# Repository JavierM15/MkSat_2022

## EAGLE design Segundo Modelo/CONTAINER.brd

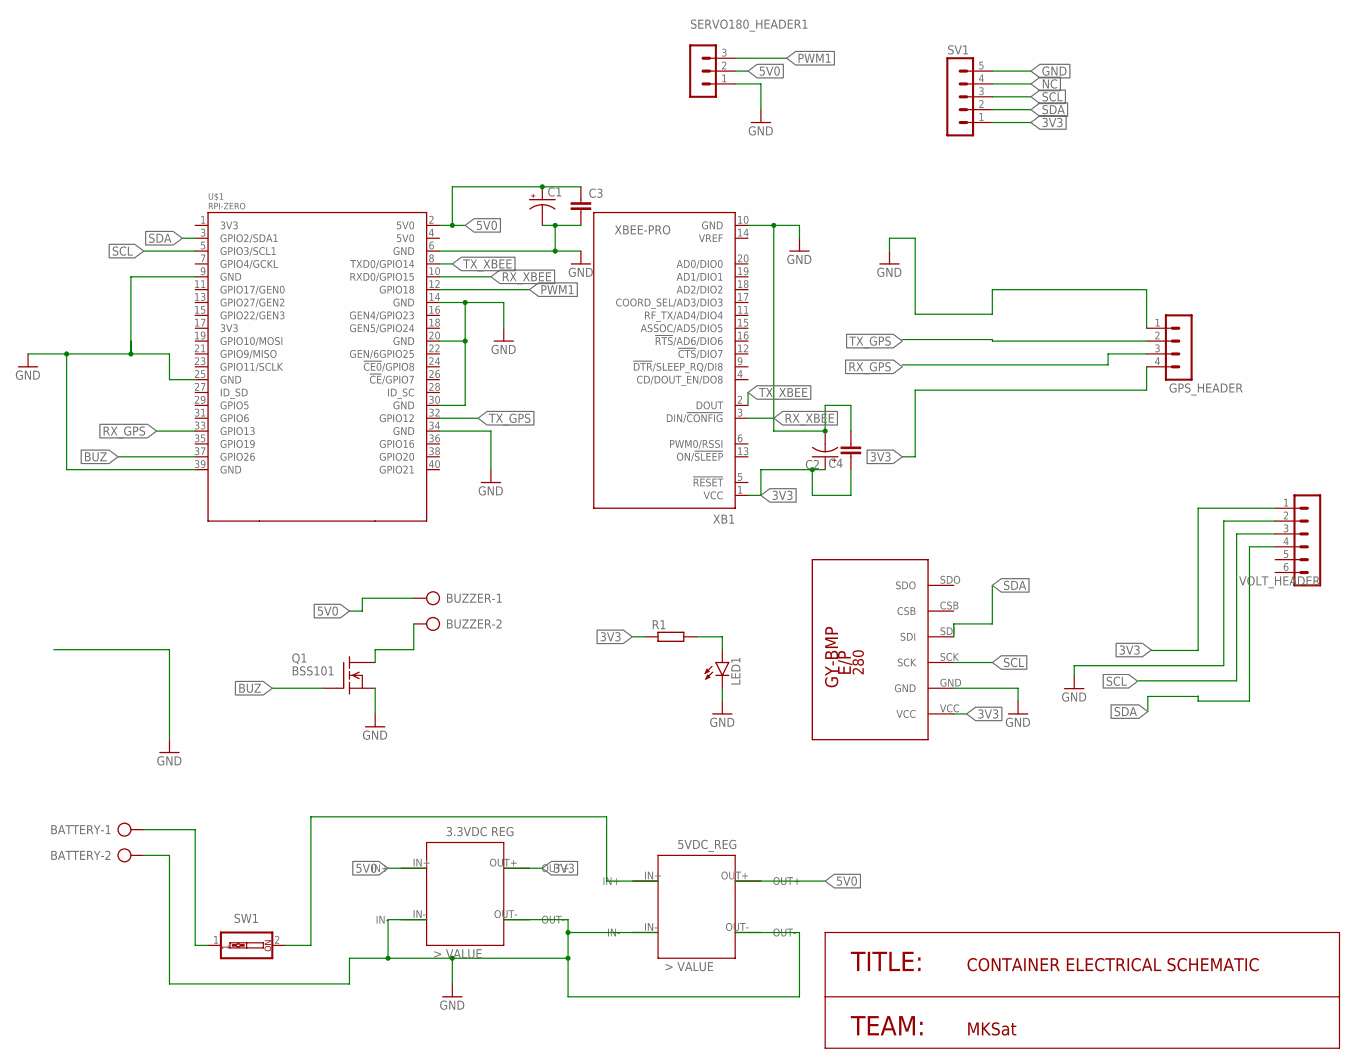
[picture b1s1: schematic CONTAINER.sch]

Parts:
BATTERY: AK500/2
BUZZER: AK500/2
C1, C2: CPOL-USTAP5-45; TAP5-45
C3, C4: C-EU050-030X075; C050-030X075
GPS_HEADER: MA04-1
LED1: LED5MM
Q1: BSS101; TO92
R1: R-EU_0207/12; 0207/12
SERVO180_HEADER1: MA03-1
SV1: MA05-1
SW1: SW_DIP-1; EDG-01
U$1: RPI-ZERO; RASPBERRYPI_BASTELSTUBE_V13_RASPI_BOARD_B+_FULL
U$4: GY-BPM280; GY-BMP280-FOOTPRINT
U$5: 3VDC_REG
U$6: 5VDC_REG
VOLT_HEADER: MA06-1
XB1: XBEE-PRO

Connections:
3V3: C2.+, C4.1, GPS_HEADER.4, R1.1, SV1.1, U$4.VCC, U$5.OUT+, VOLT_HEADER.1, XB1.1 (VCC)
5V0: BUZZER.1, C1.+, C3.1, SERVO180_HEADER1.2, U$1.2 (5V0), U$5.IN+, U$6.OUT+
BUZ: Q1.2 (G), U$1.37 (GPIO26)
GND: BATTERY.2, C1.-, C2.-, C3.2, C4.2, GPS_HEADER.1, LED1.K (C), Q1.1 (S), SERVO180_HEADER1.1, SV1.5, U$1.6 (GND), U$1.9 (GND), U$1.14 (GND), U$1.20 (GND), U$1.25 (GND), U$1.30 (GND), U$1.34 (GND), U$1.39 (GND), U$4.GND, U$5.IN-, U$5.OUT-, U$6.IN-, U$6.OUT-, VOLT_HEADER.2, XB1.10 (GND)
unnamed: LED1.A, R1.2
unnamed: BATTERY.1, SW1.1
unnamed: SW1.2, U$6.IN+
unnamed: BUZZER.2, Q1.3 (D)
NC: SV1.4
PWM1: SERVO180_HEADER1.3, U$1.12 (GPIO18)
RX_GPS: GPS_HEADER.3, U$1.33 (GPIO13)
RX_XBEE: U$1.10 (RXD0/GPIO15), XB1.3 (DIN/!CONFIG)
SCL: SV1.3, U$1.5 (GPIO3/SCL1), U$4.SCK, VOLT_HEADER.3
SDA: SV1.2, U$1.3 (GPIO2/SDA1), U$4.SDI, VOLT_HEADER.4
TX_GPS: GPS_HEADER.2, U$1.32 (GPIO12)
TX_XBEE: U$1.8 (TXD0/GPIO14), XB1.2 (DOUT)

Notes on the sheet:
TITLE:
TEAM:
CONTAINER ELECTRICAL SCHEMATIC
MKSat

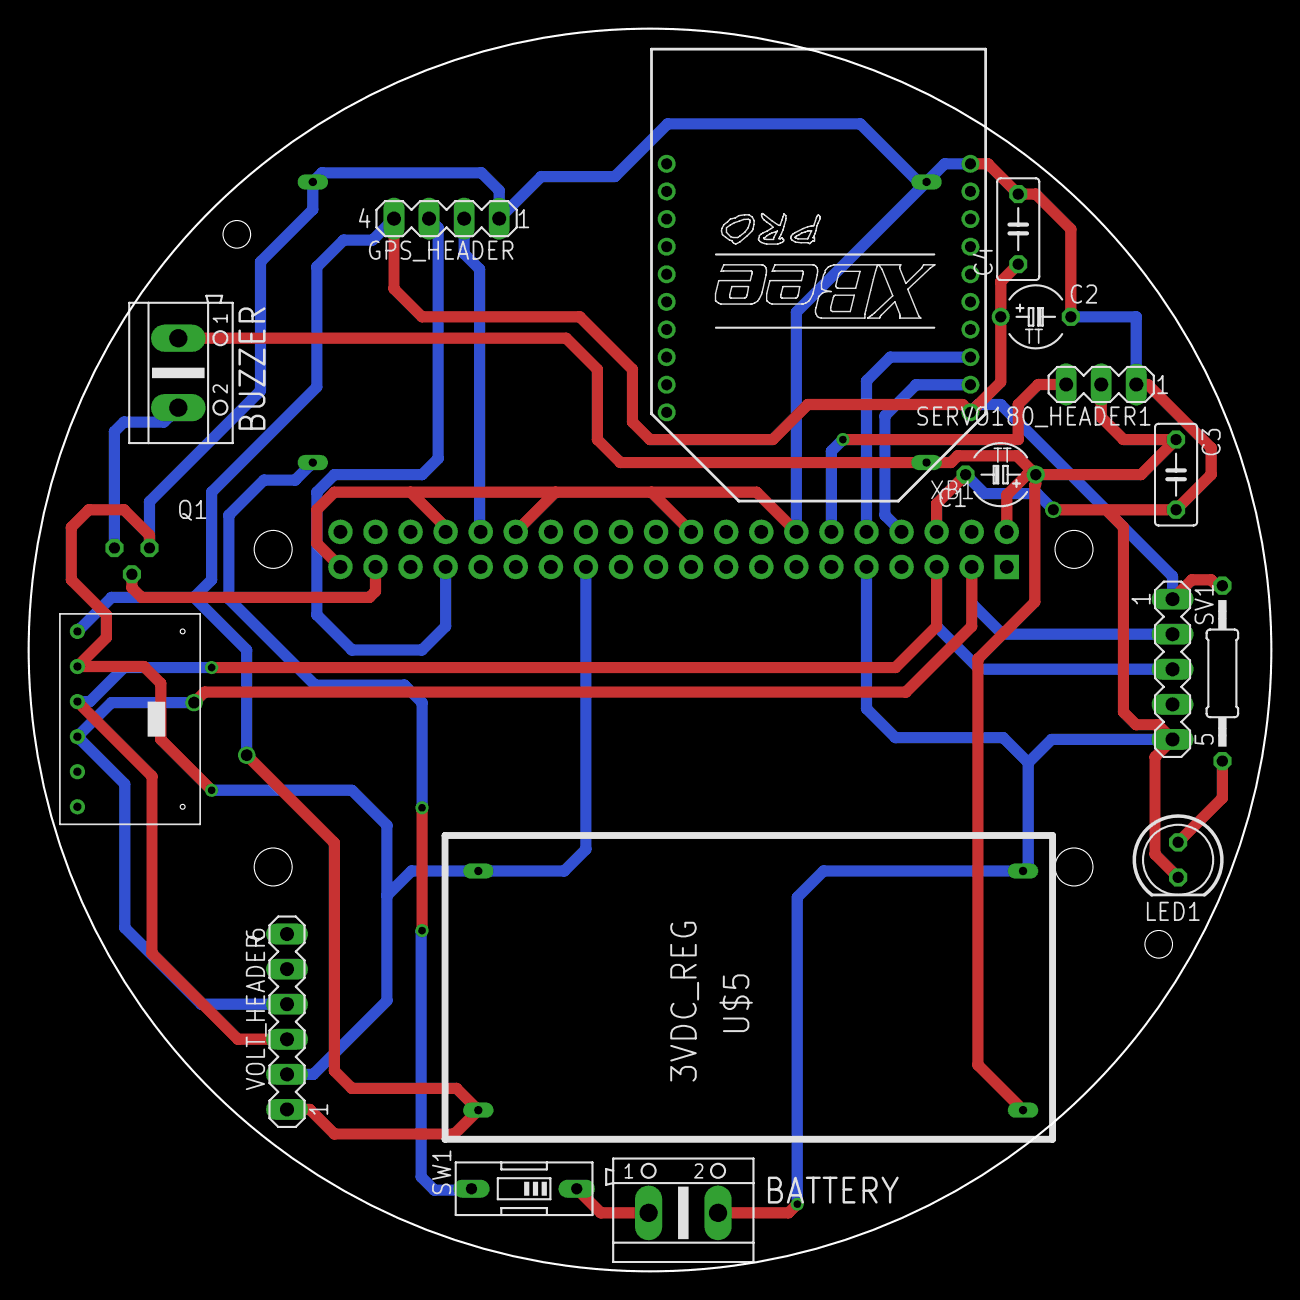
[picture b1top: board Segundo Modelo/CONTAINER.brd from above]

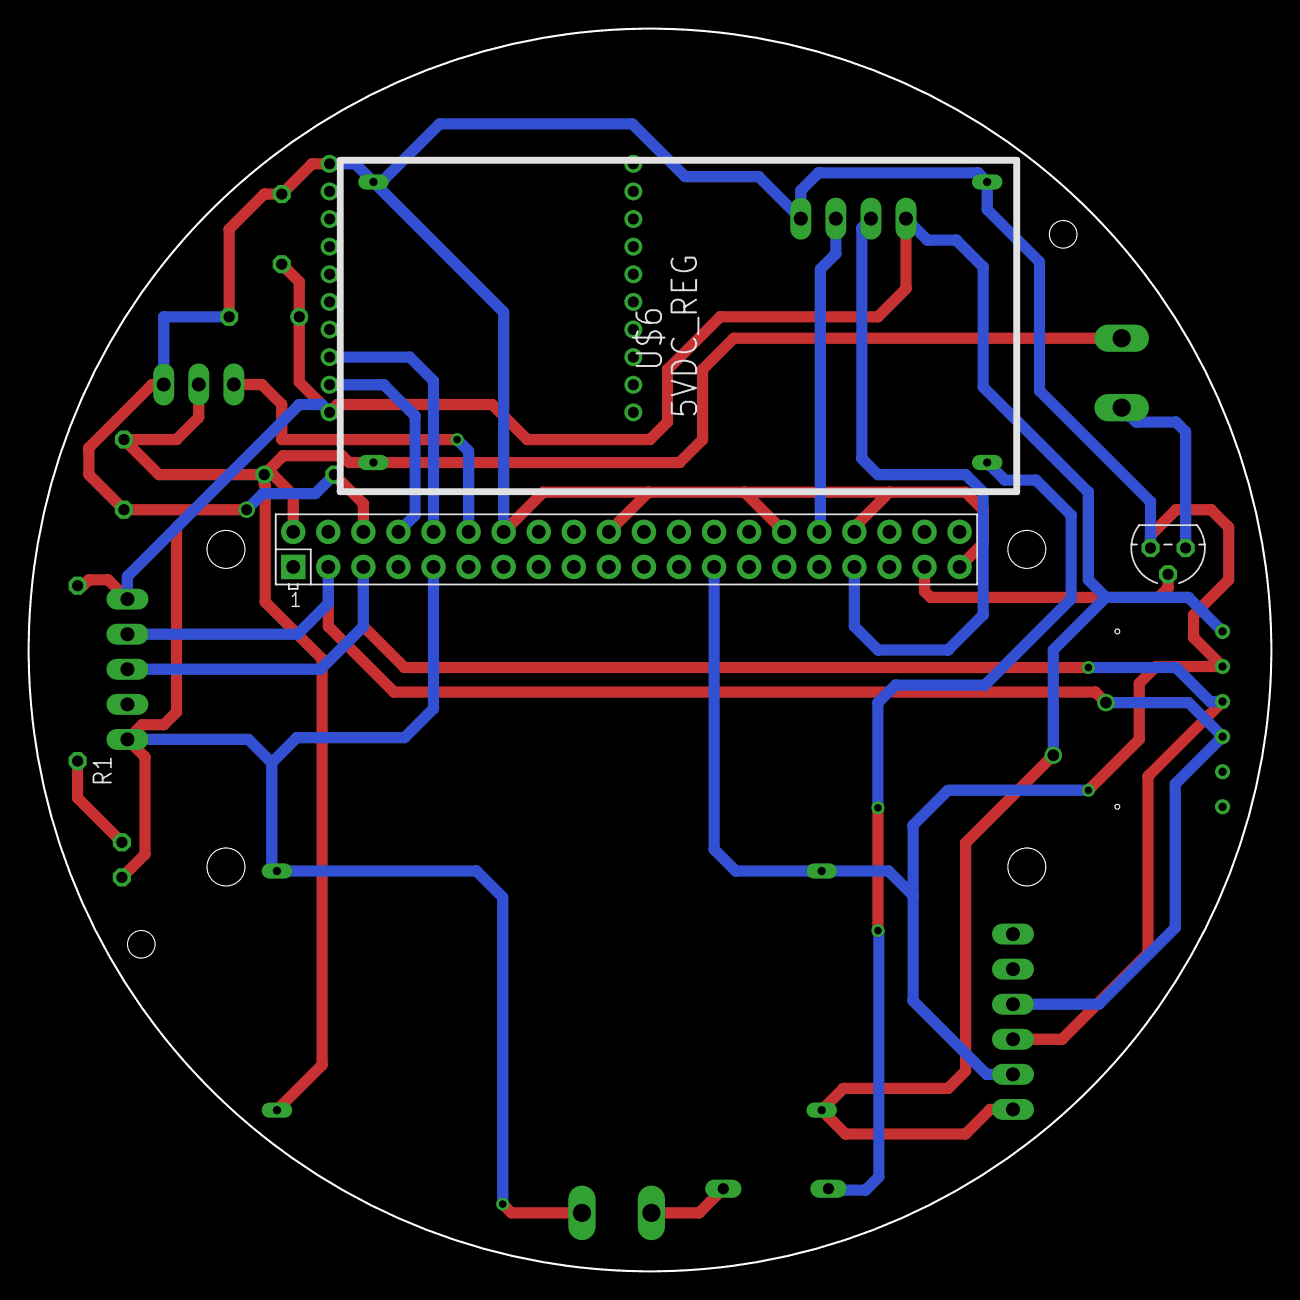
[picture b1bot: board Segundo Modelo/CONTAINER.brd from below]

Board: 2 copper layers, 90.0 x 90.0 mm, 19 parts (3 on the bottom side), 15 nets.

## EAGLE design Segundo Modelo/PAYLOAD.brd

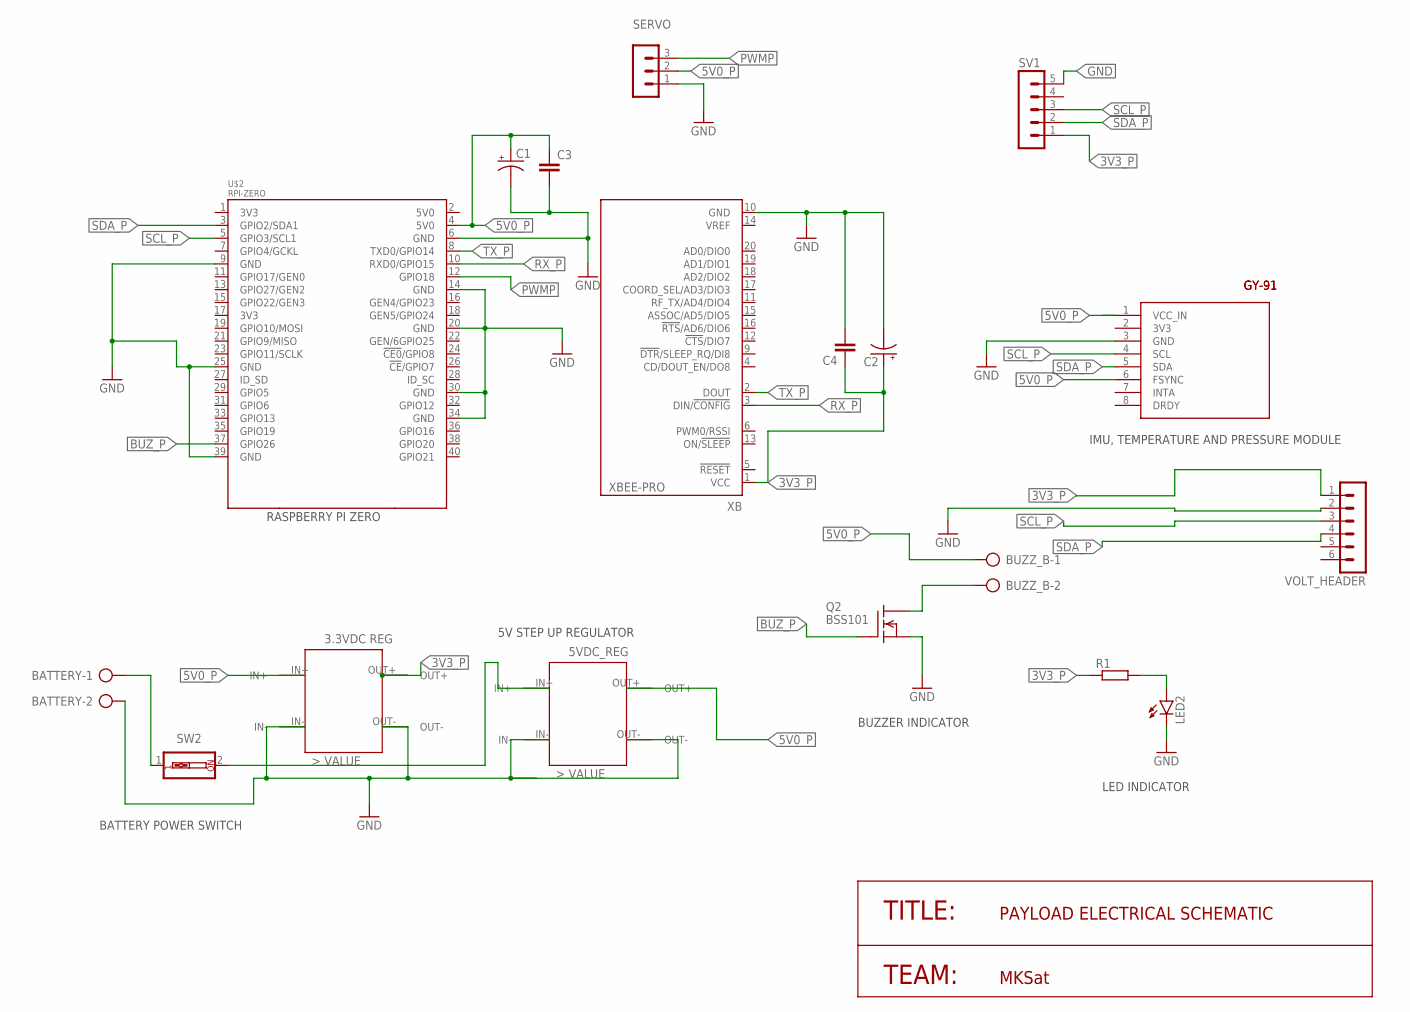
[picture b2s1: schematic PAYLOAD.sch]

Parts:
BATTERY: AK500/2
BUZZ_B: AK500/2
C1, C2: CPOL-USTAP5-45; TAP5-45
C3, C4: C-EU050-030X075; C050-030X075
GY-91_P: GY-86
LED2: LED5MM
Q2: BSS101; TO92
R1: R-EU_0207/12; 0207/12
SERVO: MA03-1
SV1: MA05-1
SW2: SW_DIP-1; EDG-01
U$1: 3VDC_REG
U$2: RPI-ZERO; RASPBERRYPI_BASTELSTUBE_V13_RASPI_BOARD_B+_FULL
U$3: 5VDC_REG
VOLT_HEADER: MA06-1
XB: XBEE-PRO

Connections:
3V3_P: C2.+, C4.1, R1.1, SV1.1, U$1.OUT+, VOLT_HEADER.1, XB.1 (VCC)
5V0_P: BUZZ_B.1, C1.+, C3.1, GY-91_P.1 (VCC_IN), GY-91_P.6 (FSYNC), SERVO.2, U$1.IN+, U$2.4 (5V0), U$3.OUT+
BUZ_P: Q2.2 (G), U$2.37 (GPIO26)
GND: BATTERY.2, C1.-, C2.-, C3.2, C4.2, GY-91_P.3 (GND), LED2.K (C), Q2.1 (S), SERVO.1, SV1.5, U$1.IN-, U$1.OUT-, U$2.6 (GND), U$2.9 (GND), U$2.14 (GND), U$2.20 (GND), U$2.25 (GND), U$2.30 (GND), U$2.34 (GND), U$2.39 (GND), U$3.IN-, U$3.OUT-, VOLT_HEADER.2, XB.10 (GND)
unnamed: BUZZ_B.2, Q2.3 (D)
unnamed: SW2.2, U$3.IN+
unnamed: BATTERY.1, SW2.1
unnamed: LED2.A, R1.2
PWMP: SERVO.3, U$2.12 (GPIO18)
RX_P: U$2.10 (RXD0/GPIO15), XB.3 (DIN/!CONFIG)
SCL_P: GY-91_P.4 (SCL), SV1.3, U$2.5 (GPIO3/SCL1), VOLT_HEADER.3
SDA_P: GY-91_P.5 (SDA), SV1.2, U$2.3 (GPIO2/SDA1), VOLT_HEADER.4
TX_P: U$2.8 (TXD0/GPIO14), XB.2 (DOUT)

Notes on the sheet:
TITLE:
TEAM:
PAYLOAD ELECTRICAL SCHEMATIC
MKSat
GY-91
IMU, TEMPERATURE AND PRESSURE MODULE
LED INDICATOR
BUZZER INDICATOR
BATTERY POWER SWITCH
5V STEP UP REGULATOR
RASPBERRY PI ZERO

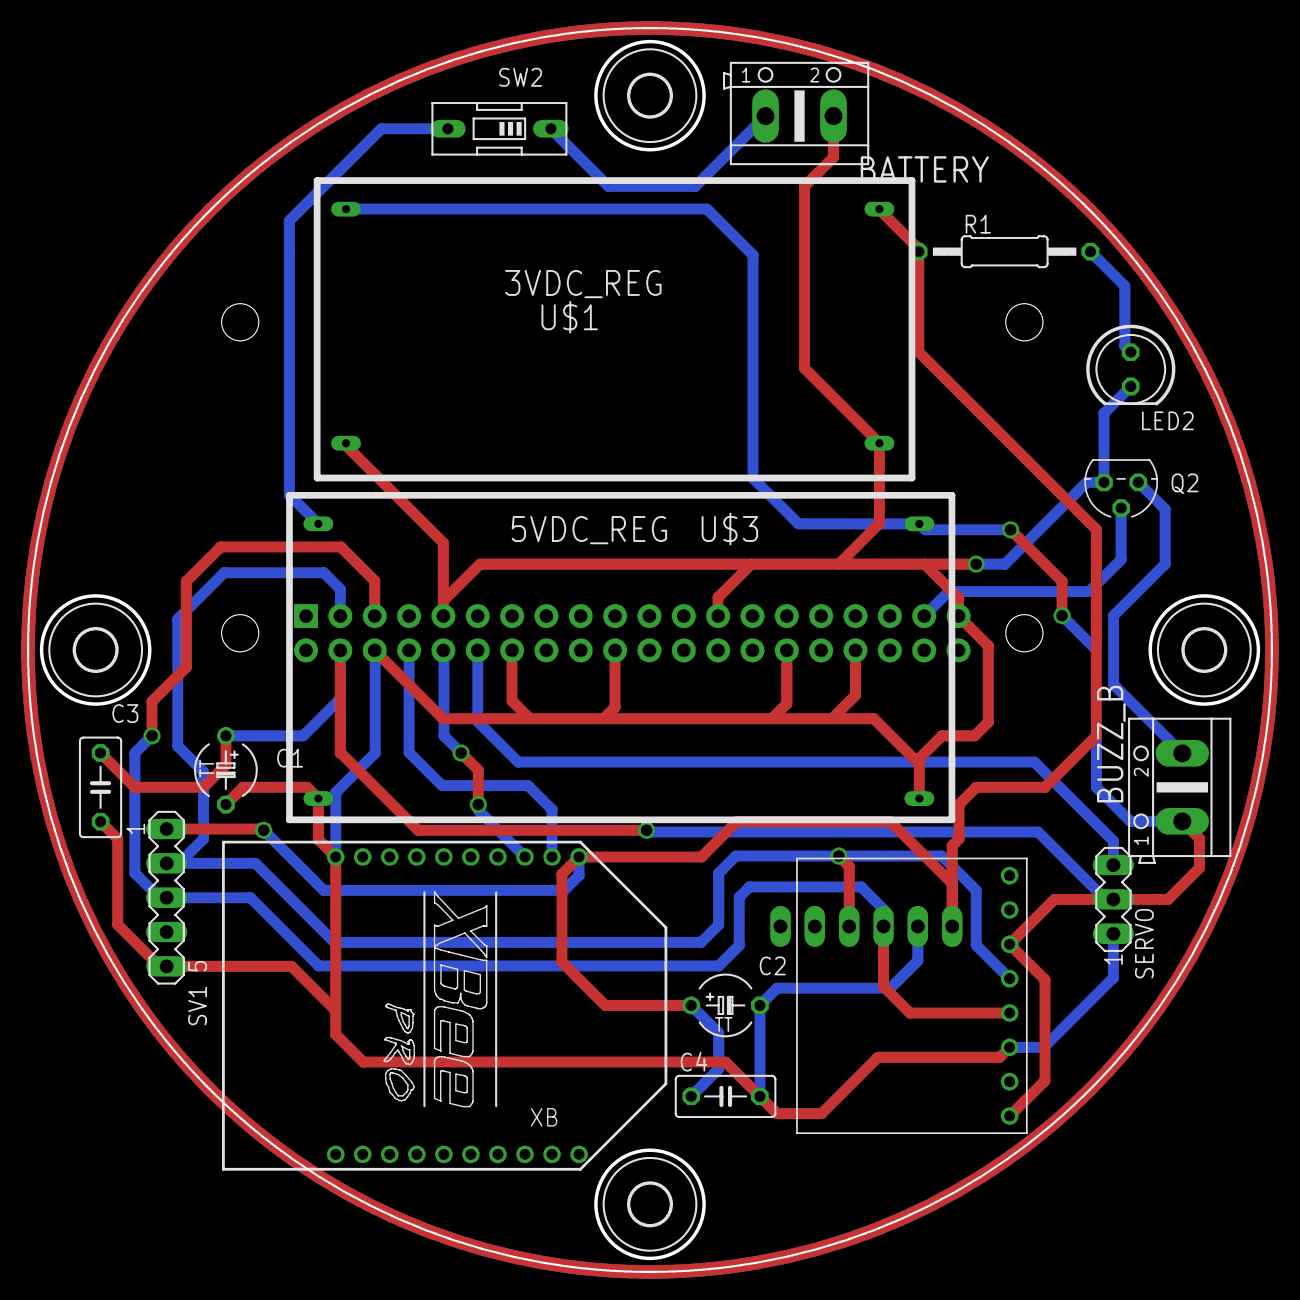
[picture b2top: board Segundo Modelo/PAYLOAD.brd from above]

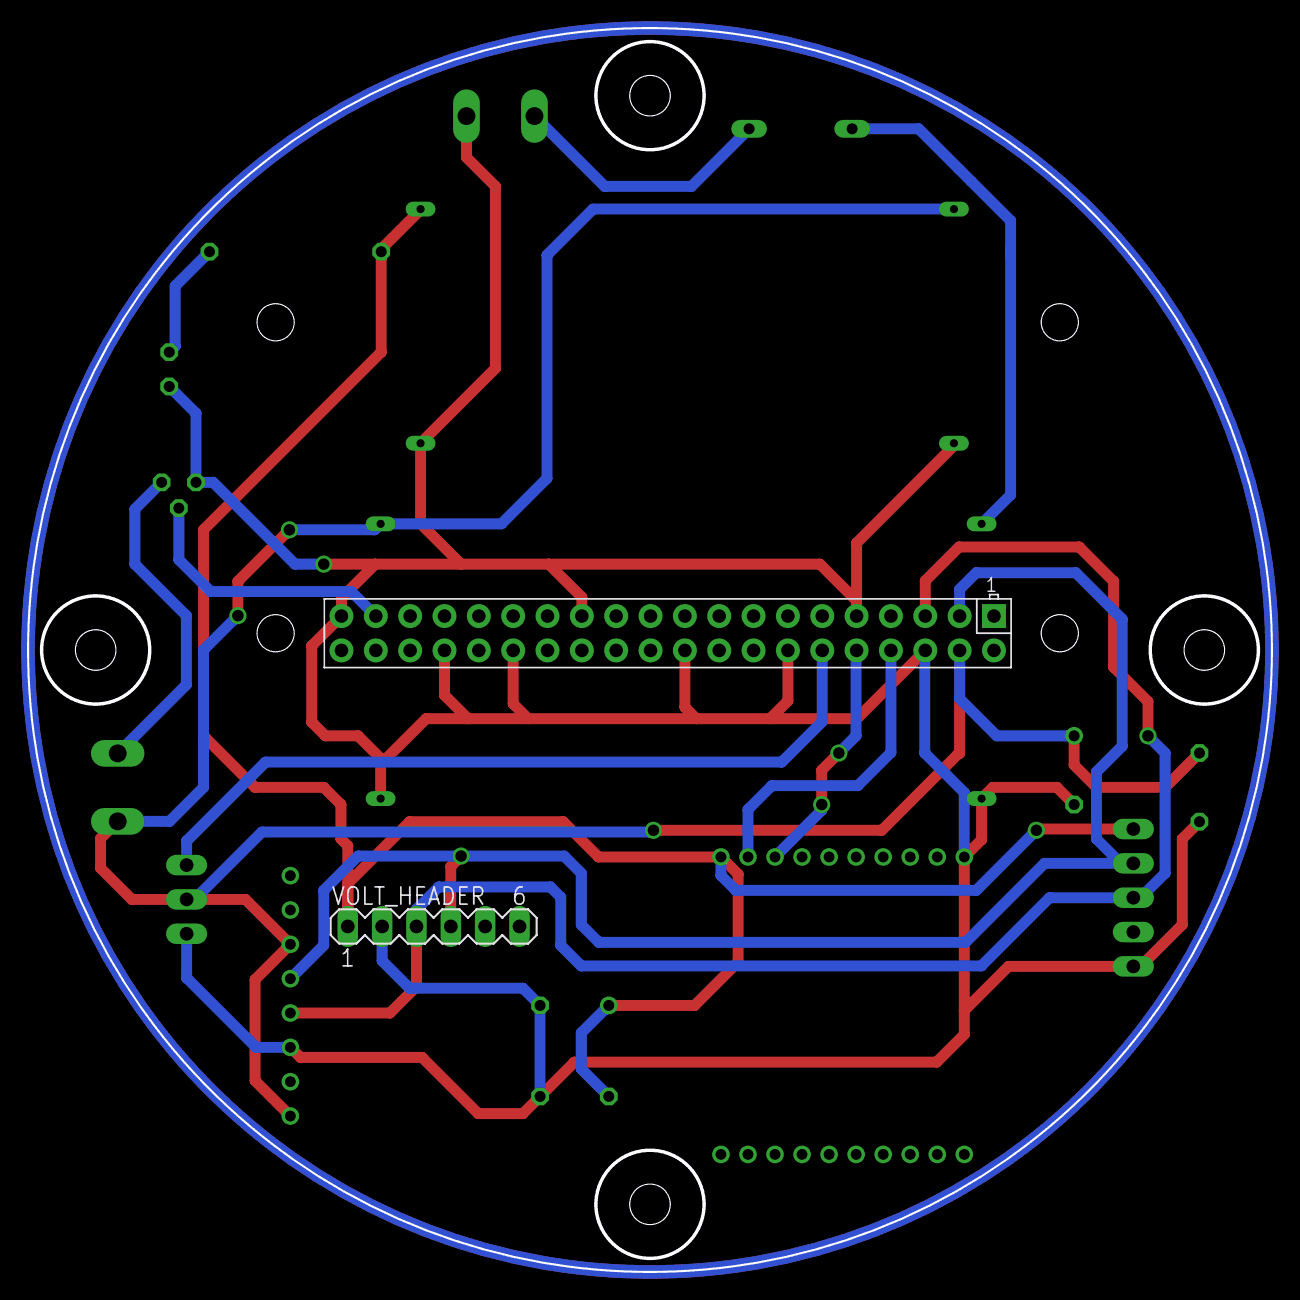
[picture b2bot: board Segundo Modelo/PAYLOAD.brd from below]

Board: 2 copper layers, 91.9 x 91.9 mm, 22 parts (2 on the bottom side), 13 nets.

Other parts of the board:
H1, H2, H3, H4: MOUNT-HOLE3.0; 3,0

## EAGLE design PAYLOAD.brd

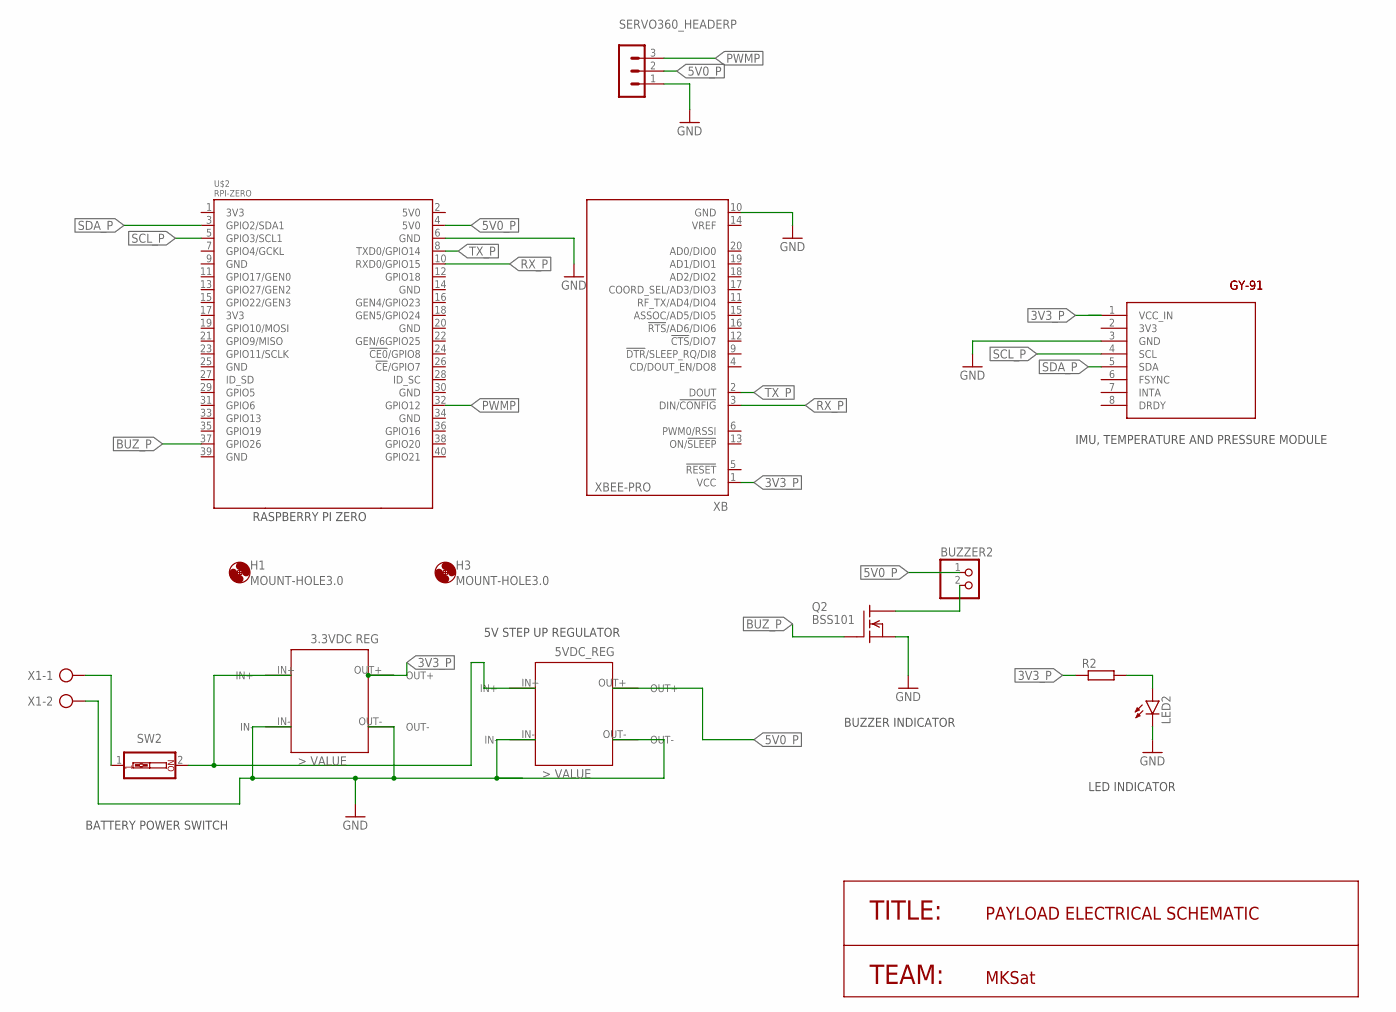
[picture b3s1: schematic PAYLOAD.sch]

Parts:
BUZZER2: PINHD-1X2/90; 1X02/90
GY-91: GY-86
H1, H3: MOUNT-HOLE3.0; 3,0
LED2: LED5MM
Q2: BSS101; TO92
R2: R-EU_0207/12; 0207/12
SERVO360_HEADERP: MA03-1
SW2: SW_DIP-1; EDG-01
U$1: 3VDC_REG
U$2: RPI-ZERO; RASPBERRYPI_BASTELSTUBE_V13_RASPI_BOARD_B+_FULL
U$3: 5VDC_REG
X1: AK500/2
XB: XBEE-PRO

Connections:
3V3_P: GY-91.1 (VCC_IN), R2.1, U$1.OUT+, XB.1 (VCC)
5V0_P: BUZZER2.1, SERVO360_HEADERP.2, U$2.4 (5V0), U$3.OUT+
BUZ_P: Q2.2 (G), U$2.37 (GPIO26)
GND: GY-91.3 (GND), LED2.K (C), Q2.1 (S), SERVO360_HEADERP.1, U$1.IN-, U$1.OUT-, U$2.6 (GND), U$3.IN-, U$3.OUT-, X1.2, XB.10 (GND)
unnamed: BUZZER2.2, Q2.3 (D)
unnamed: SW2.2, U$1.IN+, U$3.IN+
unnamed: SW2.1, X1.1
unnamed: LED2.A, R2.2
PWMP: SERVO360_HEADERP.3, U$2.32 (GPIO12)
RX_P: U$2.10 (RXD0/GPIO15), XB.3 (DIN/!CONFIG)
SCL_P: GY-91.4 (SCL), U$2.5 (GPIO3/SCL1)
SDA_P: GY-91.5 (SDA), U$2.3 (GPIO2/SDA1)
TX_P: U$2.8 (TXD0/GPIO14), XB.2 (DOUT)

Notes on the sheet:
TITLE:
TEAM:
PAYLOAD ELECTRICAL SCHEMATIC
MKSat
GY-91
IMU, TEMPERATURE AND PRESSURE MODULE
LED INDICATOR
BUZZER INDICATOR
BATTERY POWER SWITCH
5V STEP UP REGULATOR
RASPBERRY PI ZERO

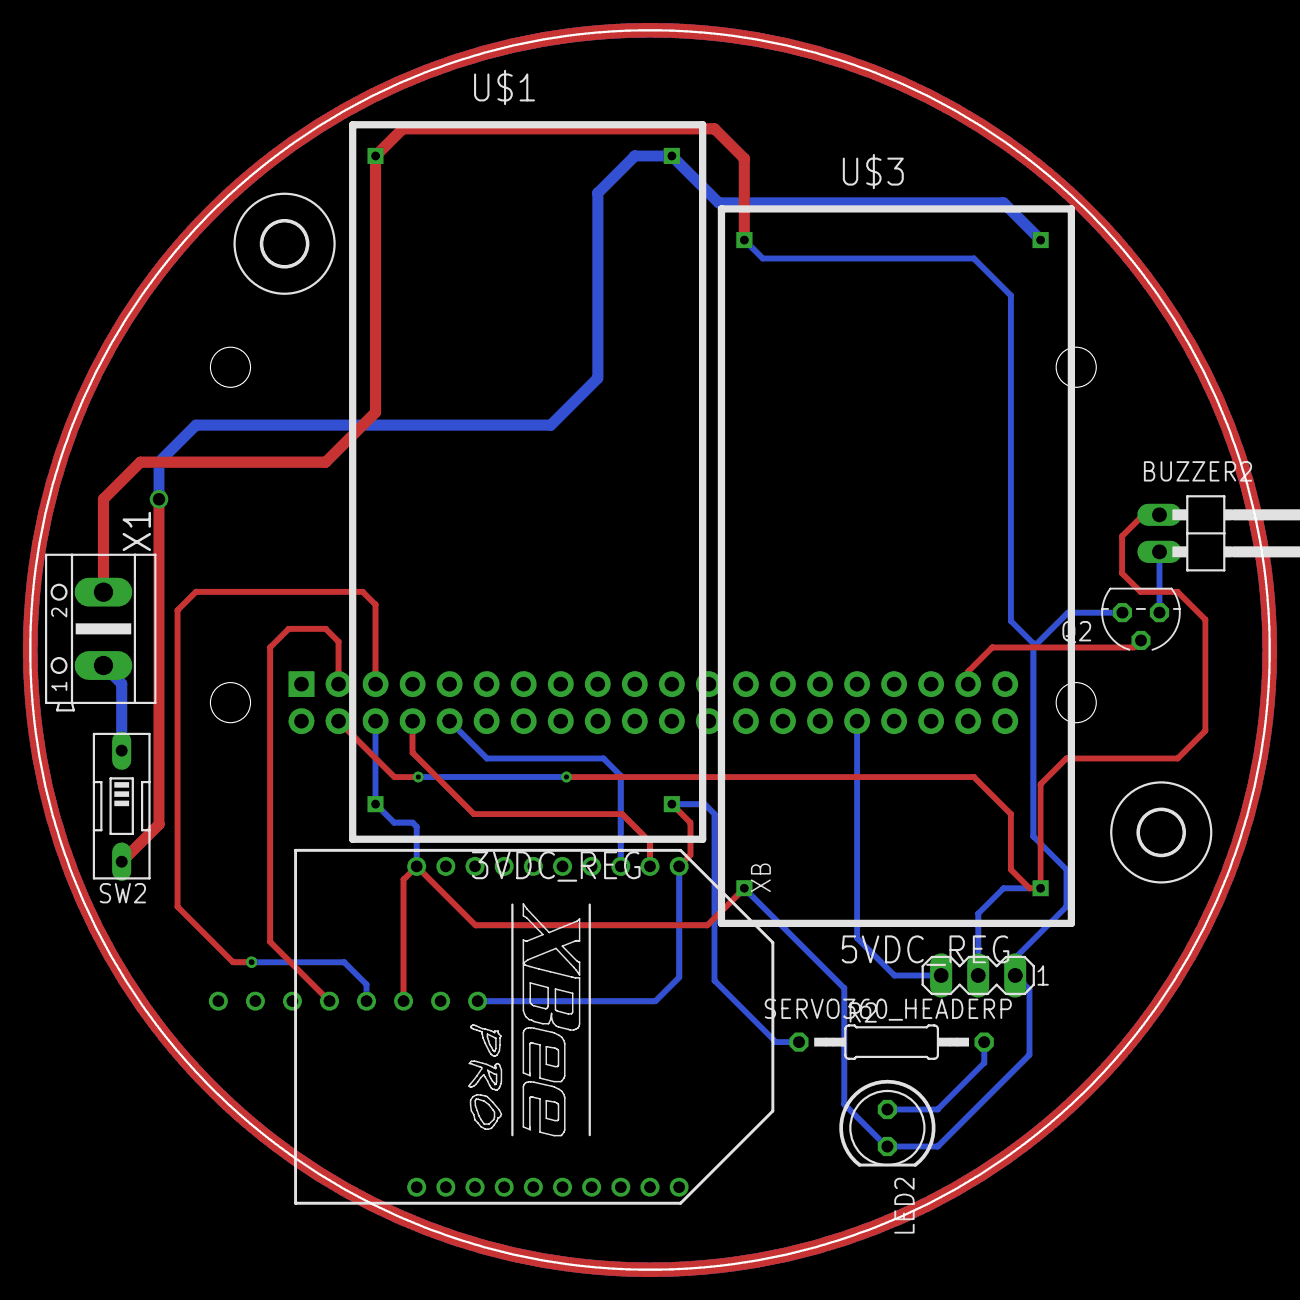
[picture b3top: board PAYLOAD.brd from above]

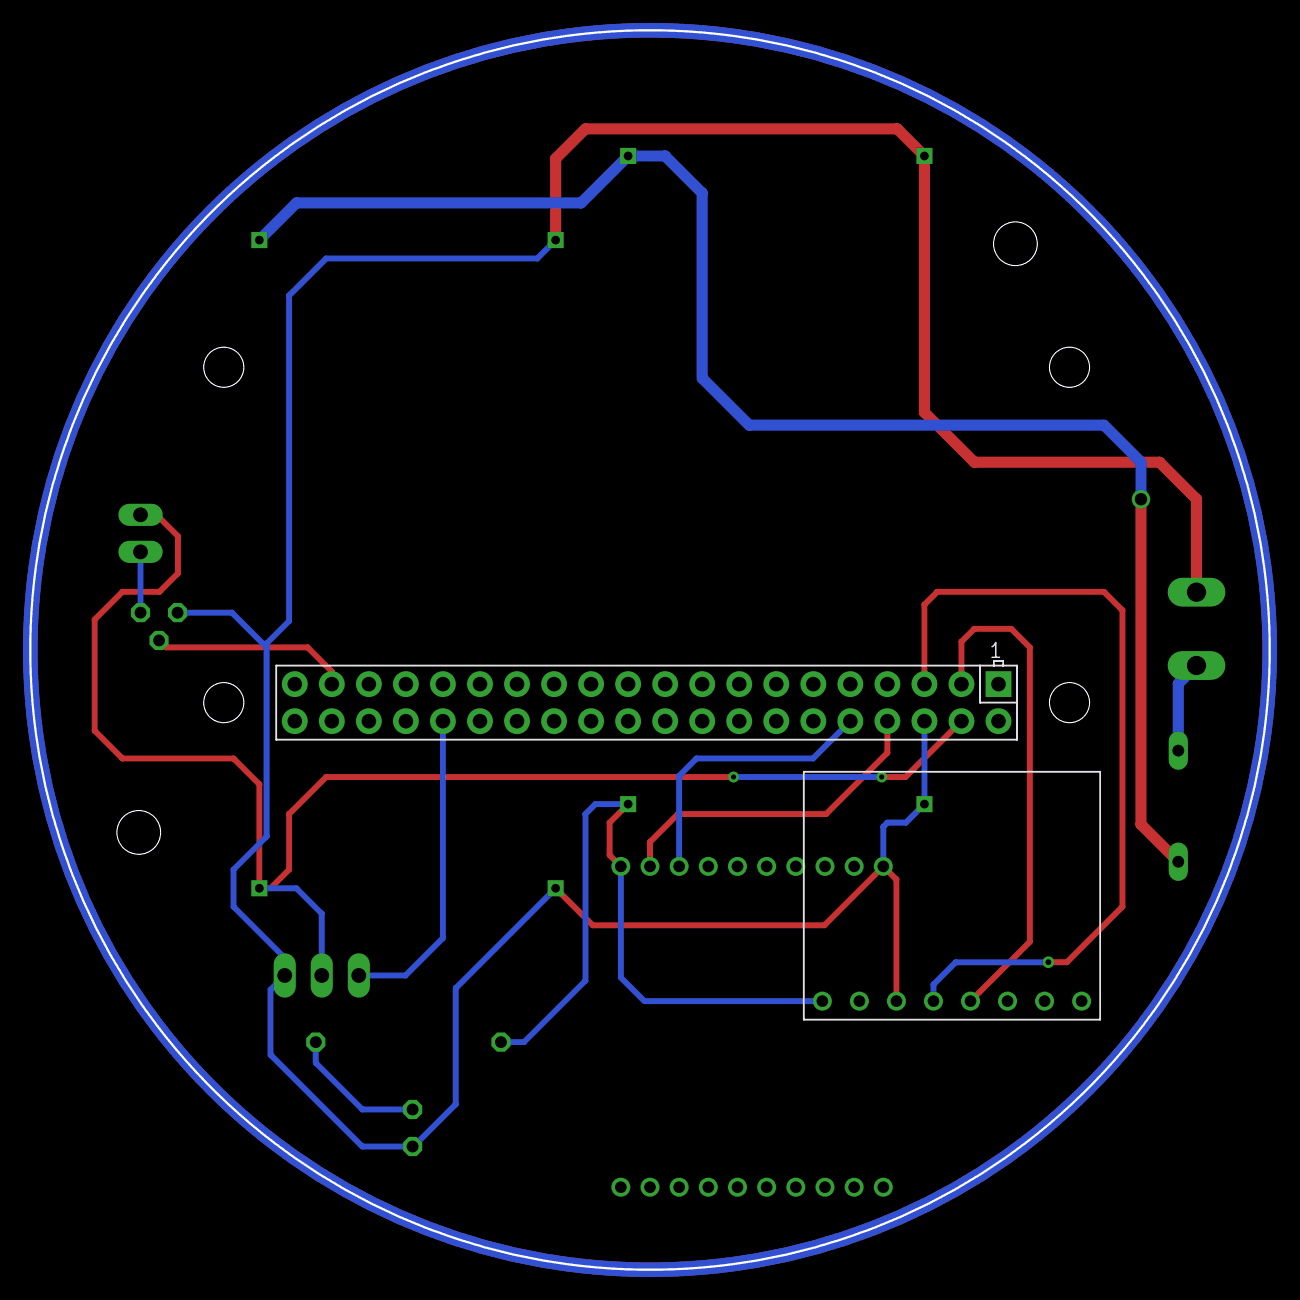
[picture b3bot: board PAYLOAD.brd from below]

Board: 2 copper layers, 85.0 x 85.0 mm, 14 parts (2 on the bottom side), 13 nets.

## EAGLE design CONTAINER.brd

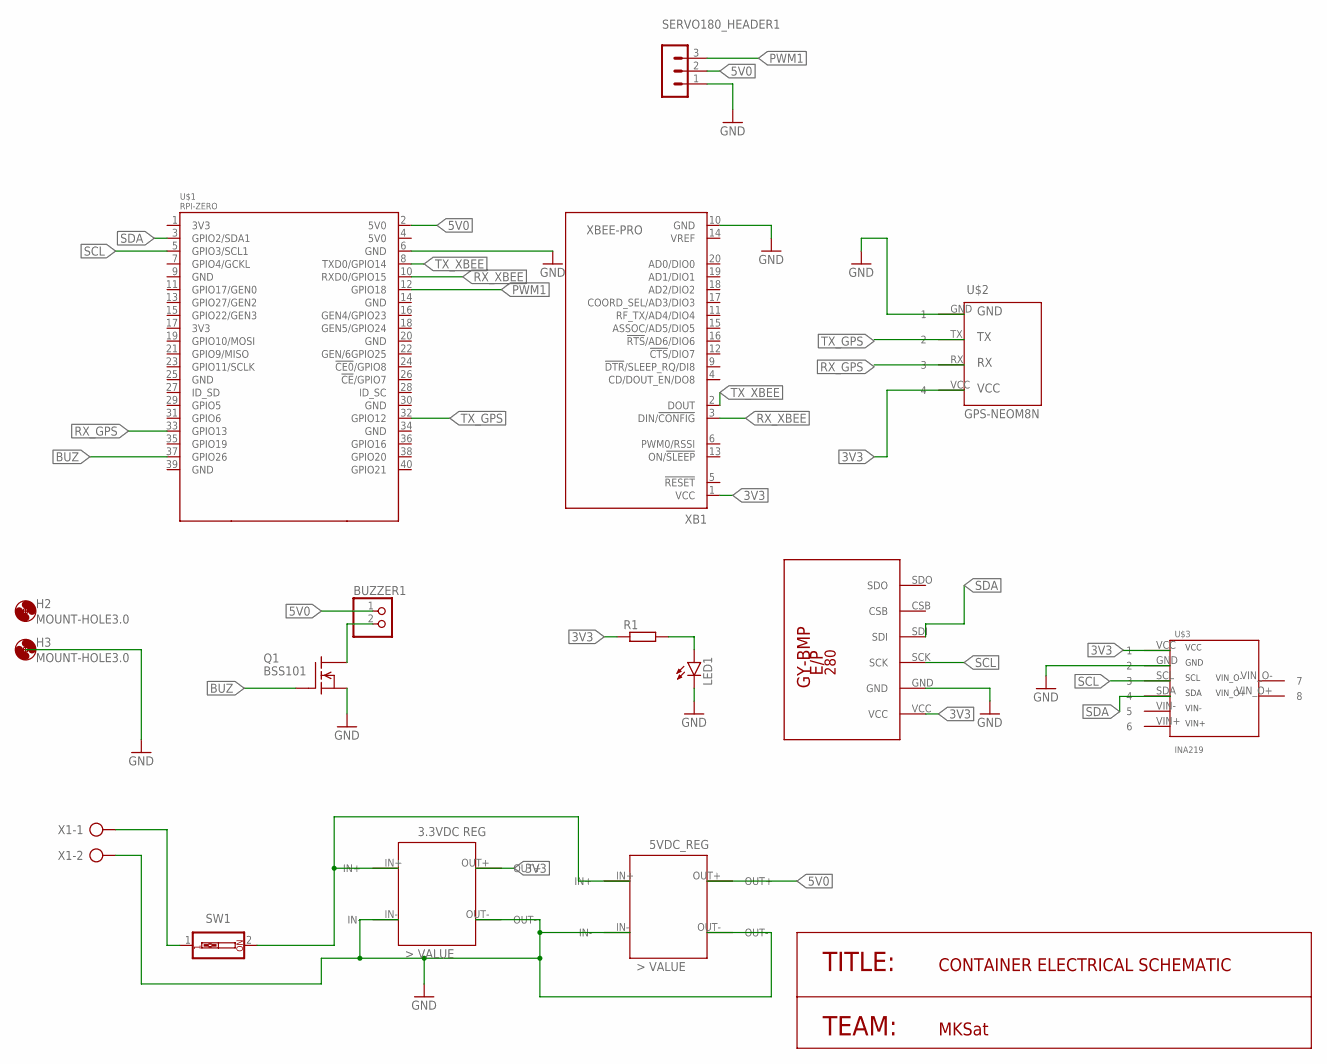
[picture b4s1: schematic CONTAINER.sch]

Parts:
BUZZER1: PINHD-1X2/90; 1X02/90
H2, H3: MOUNT-HOLE3.0; 3,0
LED1: LED5MM
Q1: BSS101; TO92
R1: R-EU_0207/12; 0207/12
SERVO180_HEADER1: MA03-1
SW1: SW_DIP-1; EDG-01
U$1: RPI-ZERO; RASPBERRYPI_BASTELSTUBE_V13_RASPI_BOARD_B+_FULL
U$2: GPS-NEOM8N; GPS_NEO_M8N
U$3: INA219; INA219_LIB
U$4: GY-BPM280; GY-BMP280-FOOTPRINT
U$5: 3VDC_REG
U$6: 5VDC_REG
X1: AK500/2
XB1: XBEE-PRO

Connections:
3V3: R1.1, U$2.VCC (4), U$3.VCC (1), U$4.VCC, U$5.OUT+, XB1.1 (VCC)
5V0: BUZZER1.1, SERVO180_HEADER1.2, U$1.2 (5V0), U$6.OUT+
BUZ: Q1.2 (G), U$1.37 (GPIO26)
GND: LED1.K (C), Q1.1 (S), SERVO180_HEADER1.1, U$1.6 (GND), U$2.GND (1), U$3.GND (2), U$4.GND, U$5.IN-, U$5.OUT-, U$6.IN-, U$6.OUT-, X1.2, XB1.10 (GND)
unnamed: LED1.A, R1.2
unnamed: SW1.1, X1.1
unnamed: SW1.2, U$5.IN+, U$6.IN+
unnamed: BUZZER1.2, Q1.3 (D)
PWM1: SERVO180_HEADER1.3, U$1.12 (GPIO18)
RX_GPS: U$1.33 (GPIO13), U$2.RX (3)
RX_XBEE: U$1.10 (RXD0/GPIO15), XB1.3 (DIN/!CONFIG)
SCL: U$1.5 (GPIO3/SCL1), U$3.SCL (3), U$4.SCK
SDA: U$1.3 (GPIO2/SDA1), U$3.SDA (4), U$4.SDI
TX_GPS: U$1.32 (GPIO12), U$2.TX (2)
TX_XBEE: U$1.8 (TXD0/GPIO14), XB1.2 (DOUT)

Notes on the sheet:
TITLE:
TEAM:
CONTAINER ELECTRICAL SCHEMATIC
MKSat

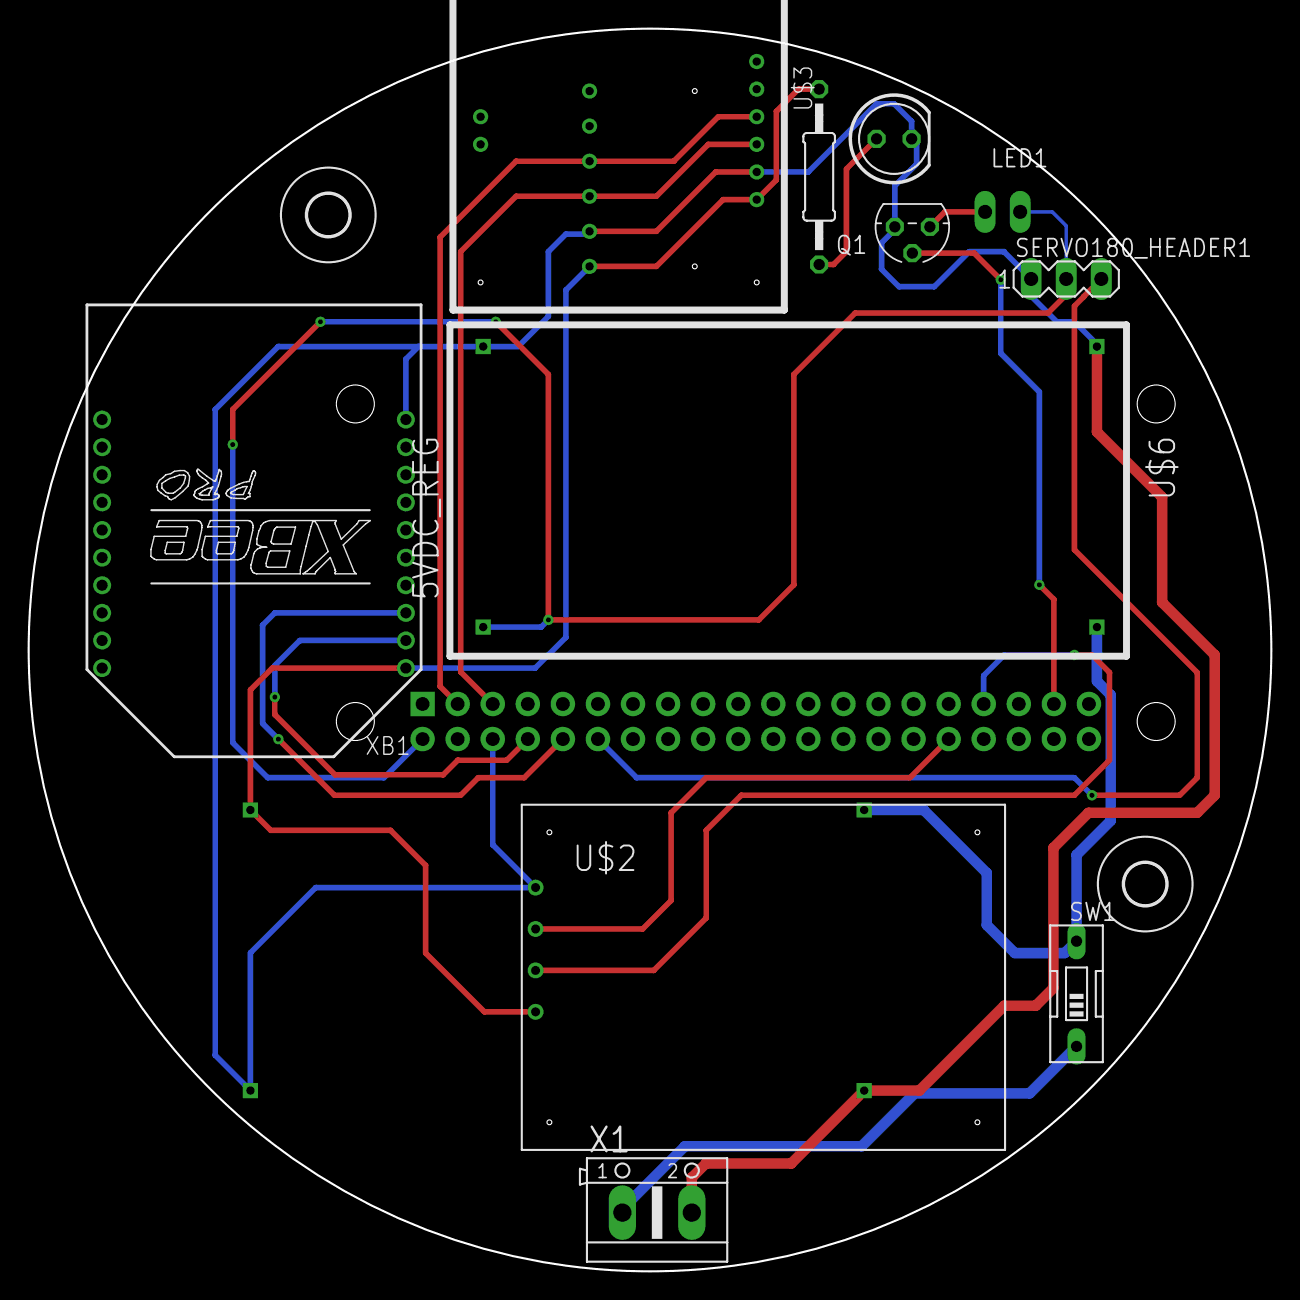
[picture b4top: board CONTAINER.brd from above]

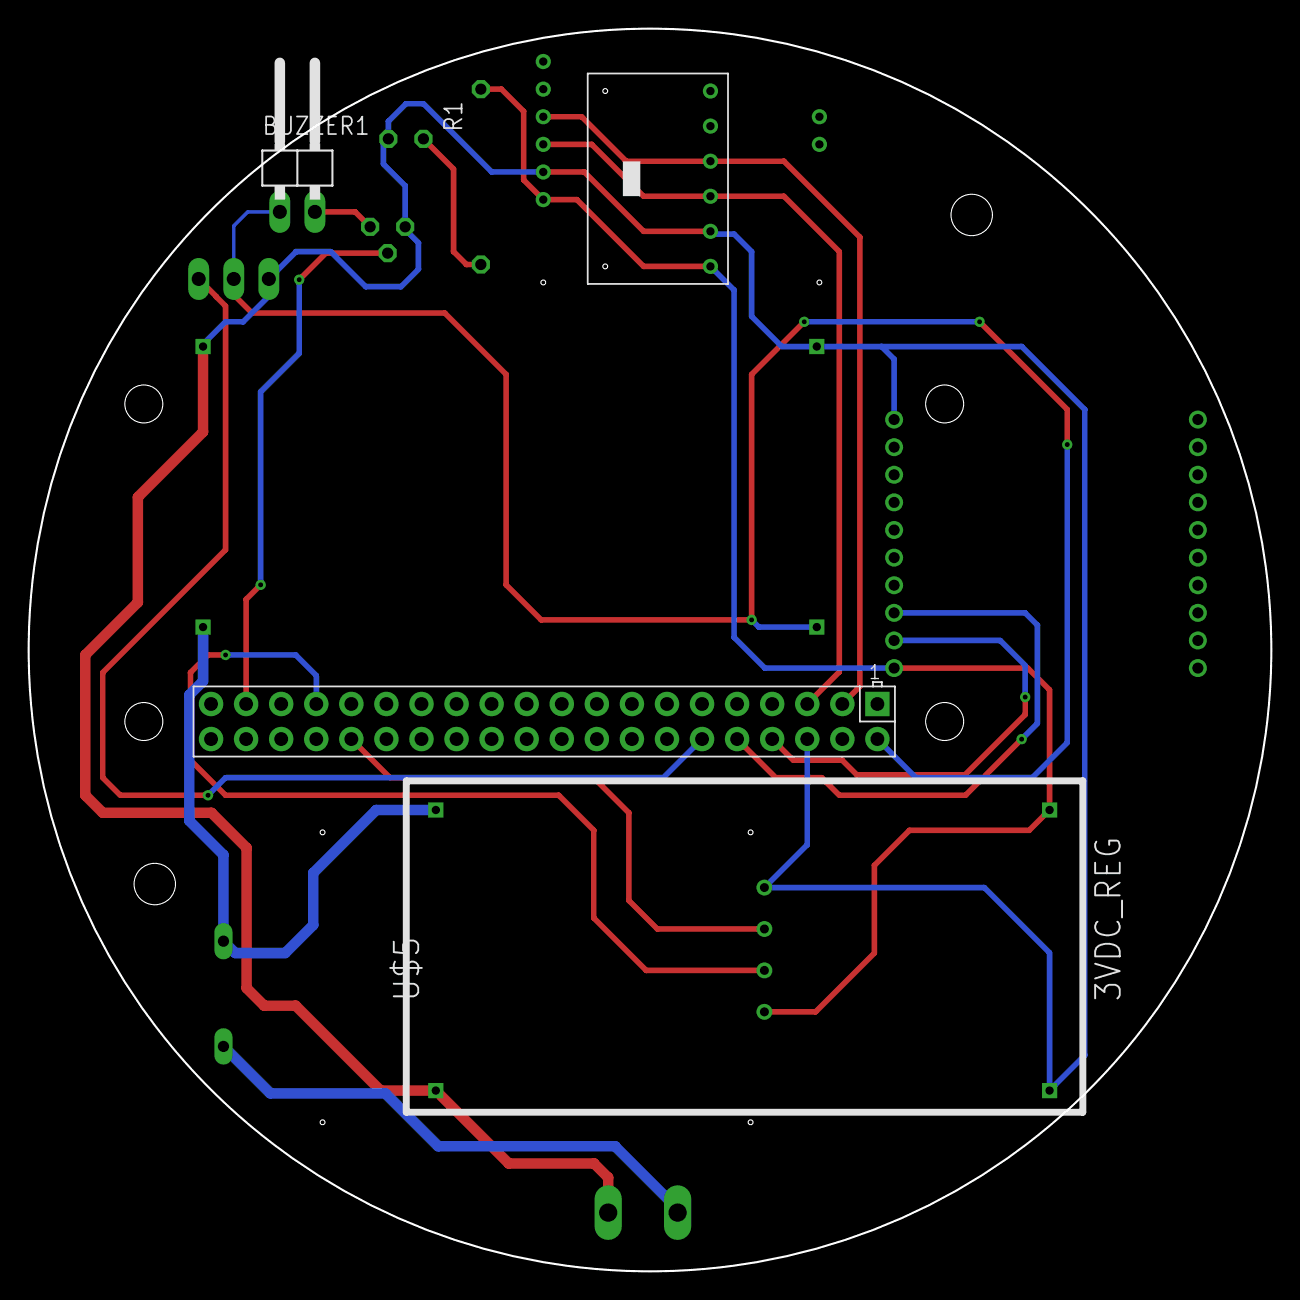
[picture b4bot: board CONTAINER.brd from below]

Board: 2 copper layers, 90.0 x 90.0 mm, 16 parts (4 on the bottom side), 15 nets.
